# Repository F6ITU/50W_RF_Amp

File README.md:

# 50W_RF_Amp, Codename Diomedes

Diomedes is a 47 dBm (50W) HF amplifier designed by Manfred XQ6FOD, and intended to be used with any baseband SDR delivering no more than 5 to 10 dBm of  output power between 1 and 54 MHz. 

The original schematic of this project 

https://ludens.cl/Electron/50Wamp/RP50Wampwm.png

as well as the assembly instructions are available at the following URL

https://ludens.cl/Electron/50Wamp/50Wamp.html

This github repository only serves to simplify the work of people who want to build this amplifier. It offers  them the Gerber files and the KiCad implementation of this project.

Thank you, Manfred, for the many developments you’ve done around the Red Pitaya board, and especially for your work on the EER support. It’s a « must read »… at least.

This amplifier is designed to follow a 14 or 16 bit Red Pitaya board or any barefoot DDC/DUC SDR board. It completes the series of devices constituting the Alexiares frontend developed by the OpenHPSDR group

https://wiki.electrolab.fr/Projets:Lab:2017:Peripheriques_Angelia

and replaces advantageously the old and outdated  Pennywhistle linear amplifier 

https://openhpsdr.org/pennywhistle.php

It should be noted that board's dimensions and mounting holes are completely compatible with Pennywhistle physical and mechanical design. In fact, Diomedes has been designed as a substitute amplifier. 
The only major difference is the input allowed power (9 dBm for Diomedes, 27 dBm max for Pennywhistle).

More powerful, more sensitive, less expensive, modern, this final stage uses a tandem of LDMOS transistors. It is perfectly matched with the Alex low pass filter 

https://wiki.electrolab.fr/Projets:Lab:2017:Peripheriques_Angelia#Alexiares_lpf

The code name Diomede was given to this amplifier to match the OpenHPSDR naming scheme. 
Diomedes, hero of the Illiad, was one of the most powerful warrior of the Argian clan, opponent of Apollo the defender of Troy. Apollo is the code name of the very first amplifier and low-pass filter tanddem proposed by the OpenHPSDR 

https://openhpsdr.org/apollo.php

So far, this github project is still under development, as long as the first Diomedes PCB  hasn’t been assembled and tested. Do NOT use these Gerber files for the moment.

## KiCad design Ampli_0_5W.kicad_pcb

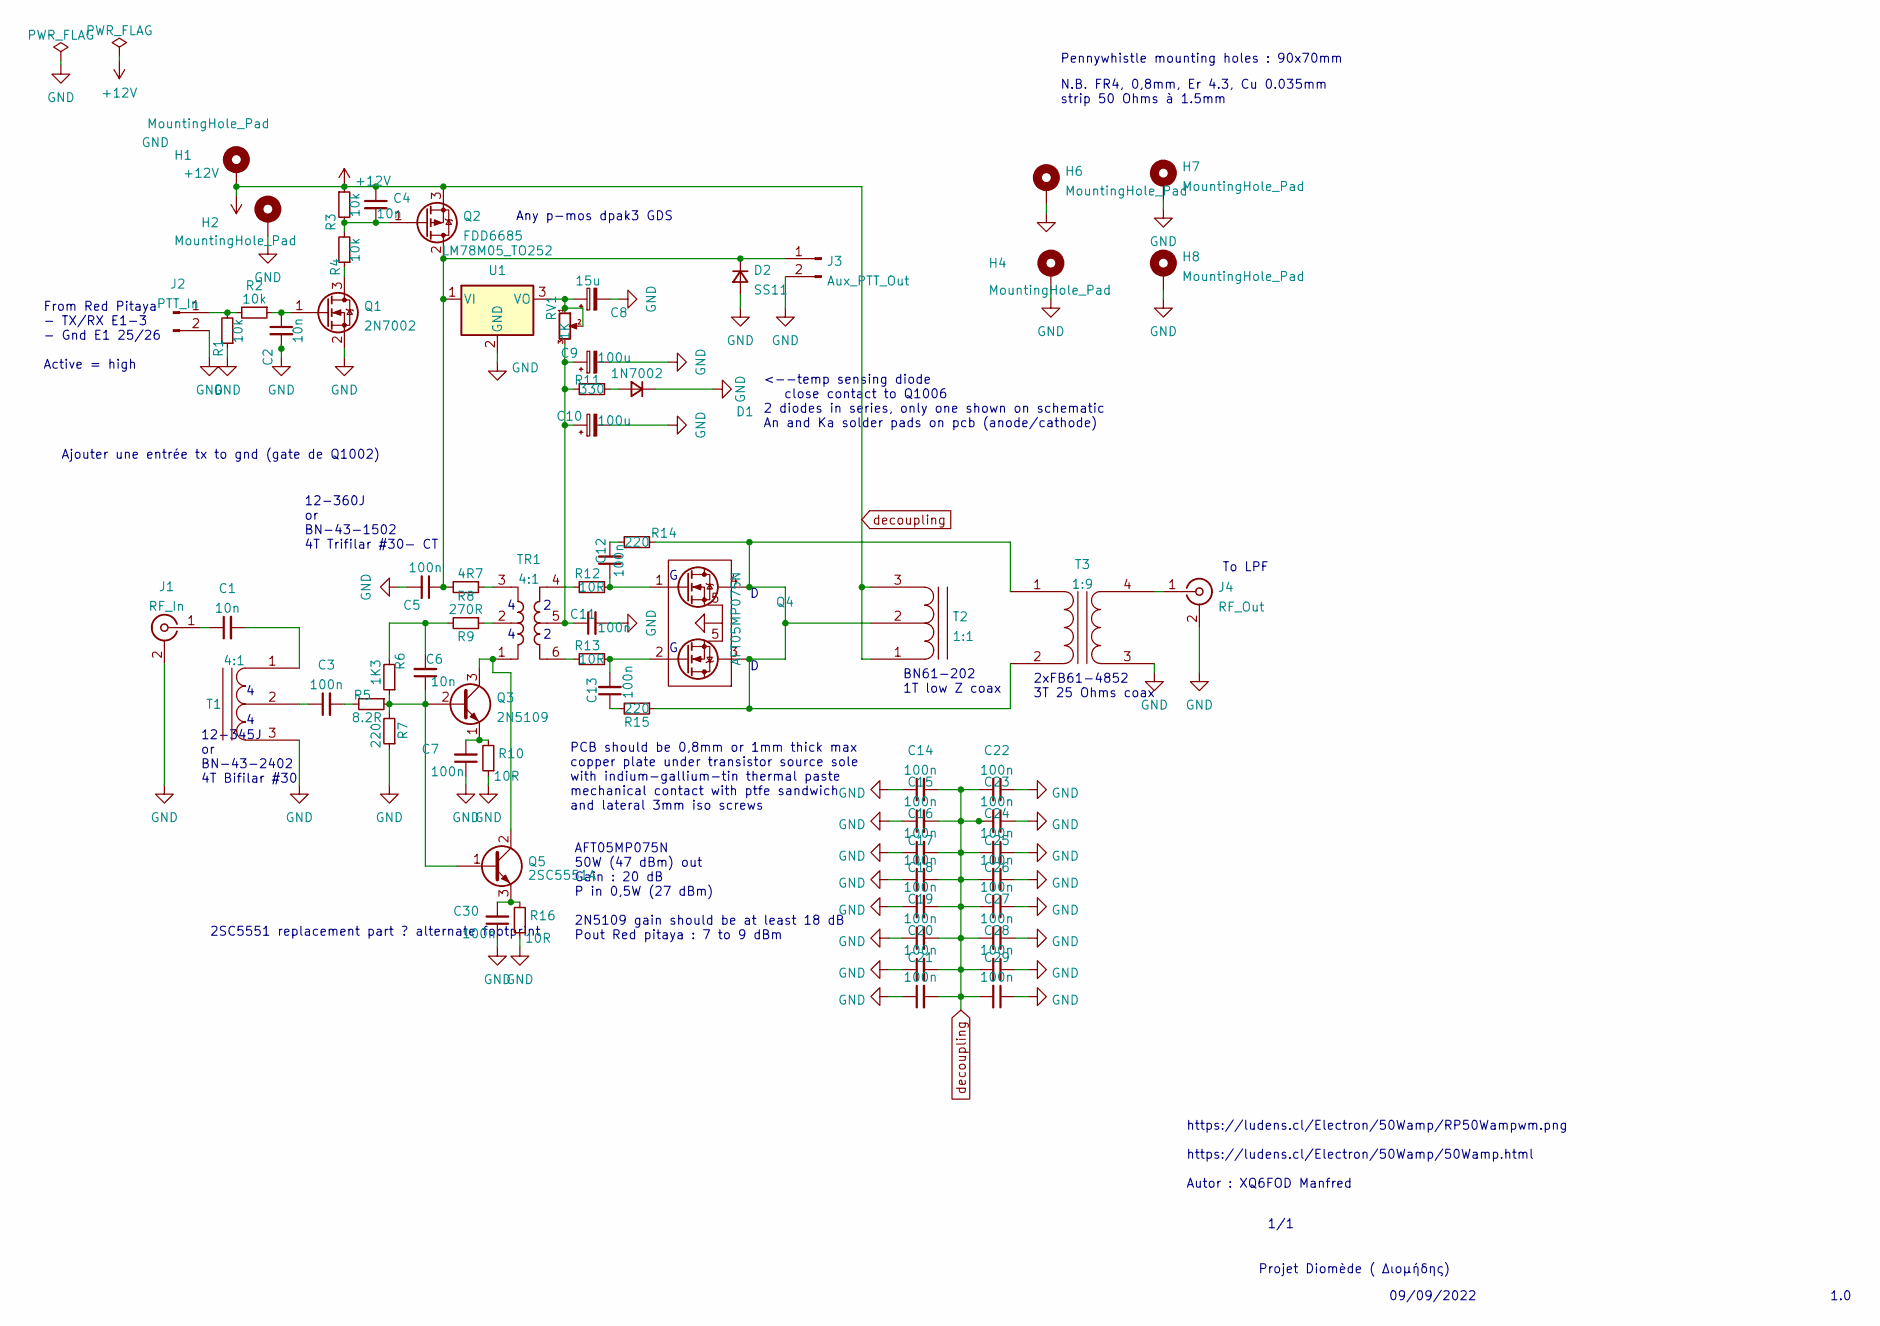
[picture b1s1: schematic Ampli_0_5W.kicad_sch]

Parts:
C1, C2, C4, C6: 10n; C_0805_2012Metric_Pad1.18x1.45mm_HandSolder
C3, C5, C7, C11: 100n; C_0805_2012Metric_Pad1.18x1.45mm_HandSolder
C8: 15u; CP_EIA-6032-28_Kemet-C_Pad2.25x2.35mm_HandSolder
C9, C10: 100u; CP_EIA-7343-31_Kemet-D_Pad2.25x2.55mm_HandSolder
C12, C13: 100n; C_1206_3216Metric_Pad1.33x1.80mm_HandSolder
C14, C15, C16, C17, C18, C19, C20, C21, C22, C23, C24, C25, C26, C27, C28, C29: 100n; C_1210_3225Metric_Pad1.33x2.70mm_HandSolder
C30: 100n; C_0603_1608Metric_Pad1.08x0.95mm_HandSolder
D1: 1N7002; D_2114_3652Metric_Pad1.85x3.75mm_HandSolder
D2: SS11; D_1812_4532Metric_Pad1.30x3.40mm_HandSolder
H1, H2, H4, H6, H7, H8: MountingHole_Pad; MountingHole_3.2mm_M3_DIN965_Pad
J1: RF_In; SMA_PINS
J2: PTT_In; Molex_KK-254_AE-6410-02A_1x02_P2.54mm_Vertical
J3: Aux_PTT_Out; Molex_KK-254_AE-6410-02A_1x02_P2.54mm_Vertical
J4: RF_Out; SMA_PINS
Q1: 2N7002; SOT-23_Handsoldering
Q2: FDD6685; TO-252-2
Q3: 2N5109; TO-39-3
Q4: AFT05MP075N
Q5: 2SC5551A; SOT-89-3
R1, R2, R3, R4: 10k; R_0805_2012Metric_Pad1.20x1.40mm_HandSolder
R5: 8.2R; R_0805_2012Metric_Pad1.20x1.40mm_HandSolder
R6: 1K3; R_0805_2012Metric_Pad1.20x1.40mm_HandSolder
R7: 220; R_0805_2012Metric_Pad1.20x1.40mm_HandSolder
R8: 4R7; R_0805_2012Metric_Pad1.20x1.40mm_HandSolder
R9: 270R; R_0805_2012Metric_Pad1.20x1.40mm_HandSolder
R10, R12, R13: 10R; R_0805_2012Metric_Pad1.20x1.40mm_HandSolder
R11: 330; R_0805_2012Metric_Pad1.20x1.40mm_HandSolder
R14, R15: 220; R_2816_7142Metric_Pad3.20x4.45mm_HandSolder
R16: 10R; R_0603_1608Metric_Pad0.98x0.95mm_HandSolder
RV1: 1K; Potentiometer_Bourns_TC33X_Vertical
T1: 4:1; BN-43-2402
T2: 1:1; BN-61-202
T3: 1:9; Dual_FB-61-4852
TR1: 4:1; BN-43-1502
U1: LM78M05_TO252; TO-252-2

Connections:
GND: C2.2, C5.2, C7.1, C8.2, C9.2, C10.2, C11.2, C14.1, C15.1, C16.1, C17.1, C18.1, C19.1, C20.1, C21.1, C22.1, C23.1, C24.1, C25.1, C26.1, C27.1, C28.1, C29.1, C30.1, D1.1 (K), D2.2 (A), H2.1, H4.1, H6.1, H7.1, H8.1, J1.2 (Ext), J2.2, J3.2, J4.2 (Ext), Q1.2 (S), R1.1, R7.1, R10.1, R16.1, T1.3 (SC), T3.3 (SA), U1.2 (GND)
unnamed: C3.2, R5.2
unnamed: C6.2, R6.2, R9.2
unnamed: C9.1, C10.1, C11.1, R11.2, RV1.3, TR1.5
unnamed: C12.1, Q4.1 (G), R12.1
unnamed: C12.2, R14.2
unnamed: C13.1, R15.2
unnamed: C13.2, Q4.2 (G), R13.1
unnamed: D1.2 (A), R11.1
unnamed: C5.1, D2.1 (K), J3.1, Q2.2 (D), R8.2, U1.1 (VI)
unnamed: C1.1, J1.1 (In)
unnamed: J2.1, R1.2, R2.2
unnamed: J4.1 (In), T3.4 (SB)
unnamed: Q1.3 (D), R4.1
unnamed: C2.1, Q1.1 (G), R2.1
unnamed: C4.2, Q2.1 (G), R3.2, R4.2
unnamed: C6.1, Q3.2 (B), Q5.1 (B), R5.1, R6.1, R7.2
unnamed: Q3.3 (C), Q5.2 (C), TR1.1
unnamed: C7.2, Q3.1 (E), R10.2
unnamed: C30.2, Q5.3 (E), R16.2
unnamed: R8.1, TR1.3
unnamed: R9.1, TR1.2
unnamed: R12.2, TR1.4
unnamed: R13.2, TR1.6
unnamed: C1.2, T1.1 (SA)
unnamed: C3.1, T1.2 (SB)
unnamed: Q4.3 (D), Q4.4 (D), R14.1, R15.1, T2.2 (SB), T3.1 (AA), T3.2 (AB)
unnamed: C8.1, RV1.1, RV1.2, U1.3 (VO)
decoupling: C4.1, C14.2, C15.2, C16.2, C17.2, C18.2, C19.2, C20.2, C21.2, C22.2, C23.2, C24.2, C25.2, C26.2, C27.2, C28.2, C29.2, H1.1, Q2.3 (S), R3.1, T2.1 (SA), T2.3 (SC)

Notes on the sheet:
To LPF
4 4
12-360J or BN-43-1502 4T Trifilar #30- CT
09/09/2022
Projet Diomède ( Διομήδης)
BN61-202 1T low Z coax
AFT05MP075N 50W (47 dBm) out Gain : 20 dB P in 0,5W (27 dBm) 2N5109 gain should be at least 18 dB Pout Red pitaya : 7 to 9 dBm
Pennywhistle mounting holes : 90x70mm
2xFB61-4852 3T 25 Ohms coax
2SC5551 replacement part ? alternate footprint
N.B. FR4, 0,8mm, Er 4.3, Cu 0.035mm strip 50 Ohms à 1.5mm
12-345J or BN-43-2402 4T Bifilar #30
PCB should be 0,8mm or 1mm thick max copper plate under transistor source sole with indium-gallium-tin thermal paste mechanical contact with ptfe sandwich and lateral 3mm iso screws
Ajouter une entrée tx to gnd (gate de Q1002)
1/1
https://ludens.cl/Electron/50Wamp/RP50Wampwm.png https://ludens.cl/Electron/50Wamp/50Wamp.html Autor : XQ6FOD Manfred
2 2
Any p-mos dpak3 GDS
From Red Pitaya - TX/RX E1-3 - Gnd E1 25/26 Active = high
D D
<--temp sensing diode close contact to Q1006 2 diodes in series, only one shown on schematic An and Ka solder pads on pcb (anode/cathode)
1.0
G G

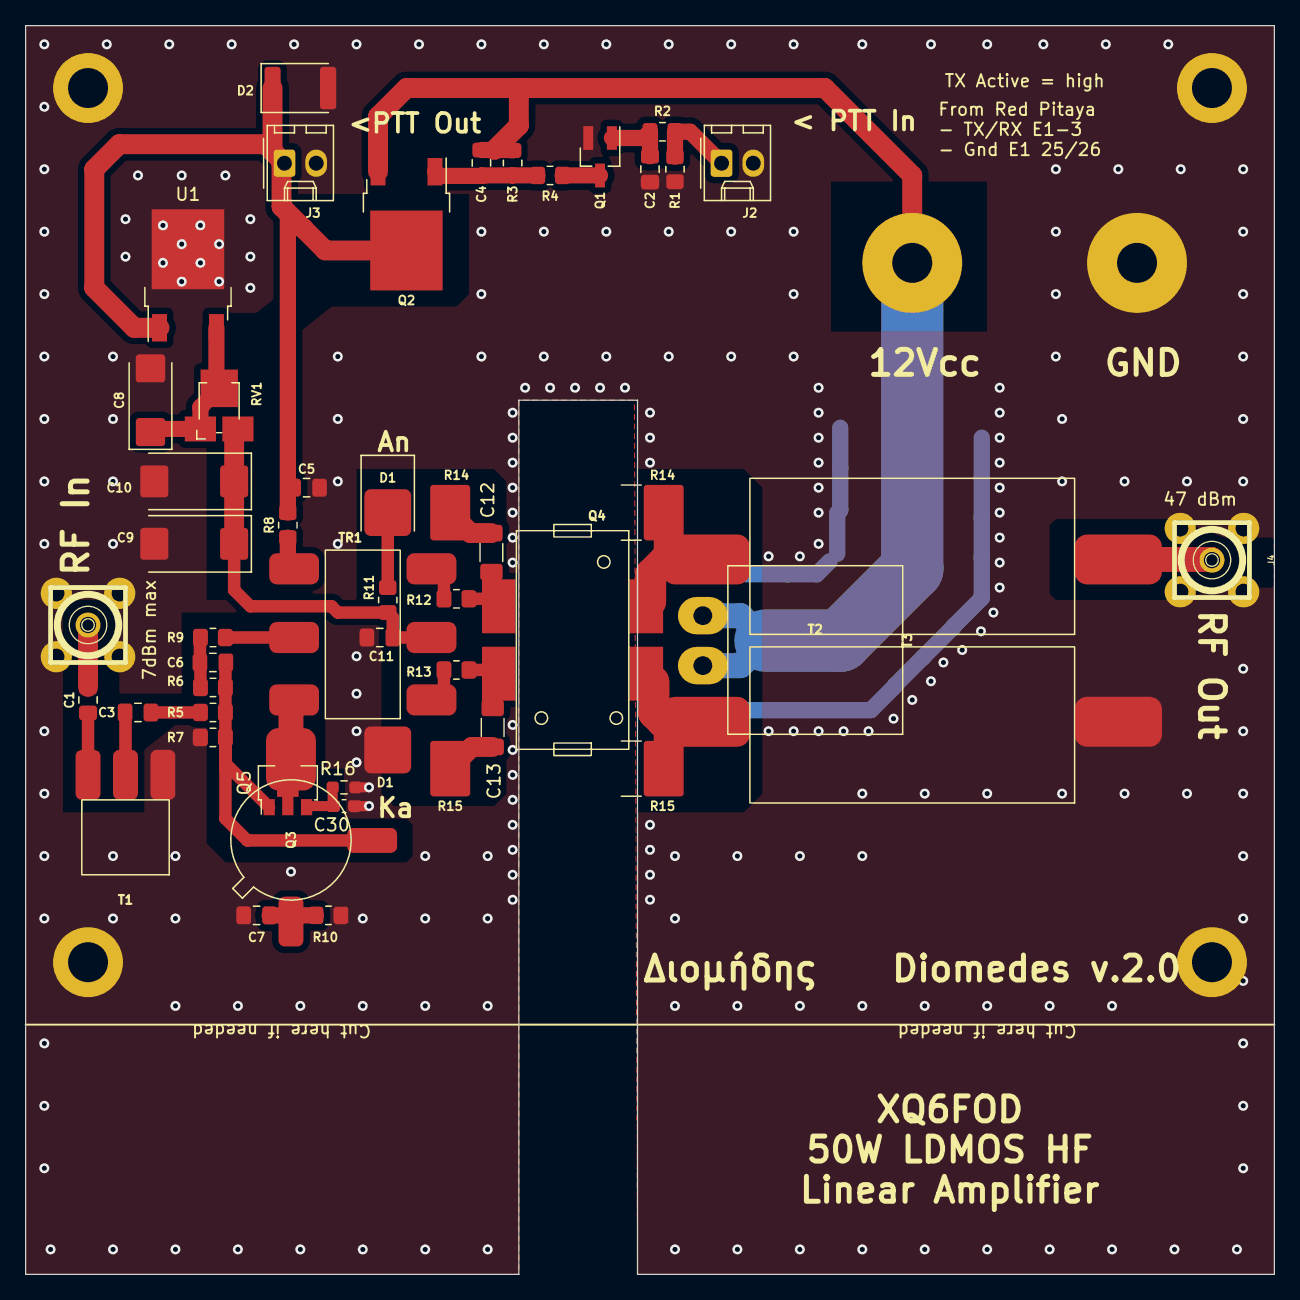
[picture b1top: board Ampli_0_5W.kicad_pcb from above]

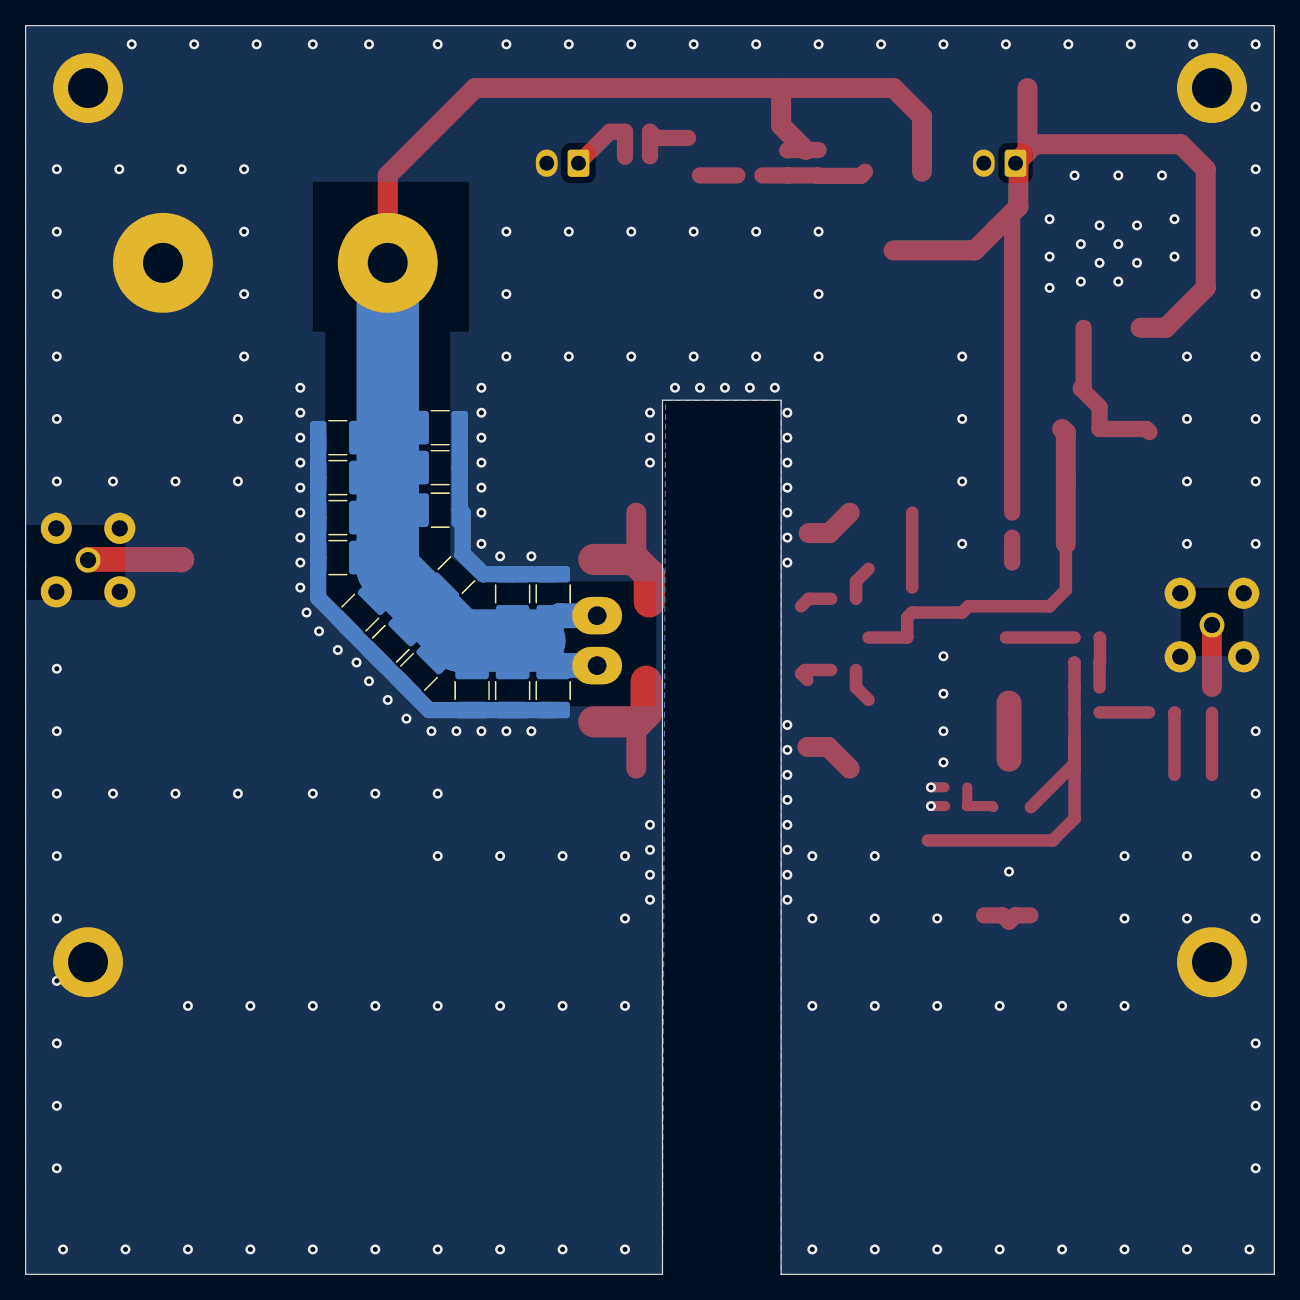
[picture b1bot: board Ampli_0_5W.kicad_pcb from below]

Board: 2 copper layers, 100.0 x 100.0 mm, 69 parts (16 on the bottom side), 29 nets.

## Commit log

2022-09-09 first commit before proto
2022-09-09 picture and pdf schematic added
2022-09-09 minor corrections
2022-09-18 release 2.0, shorter drain path
2022-09-27 shorten drain circuit, new gerber, new ibom
2022-10-12 PCB V2 final
2023-02-12 Diomedes V1.0 final with correct psu, bias & drain trace
2023-02-12 new 3D rendering
2023-02-12 new V1.0 Gerber, new ReadMe
2023-02-12 Diomedes V2.0 final, bias OK
2023-02-14 new ibom, BEWARE, KICAD 7.0 FILE FORMAT
2023-02-14 Kicad 7, new iBom, new temp diode cabling
2023-02-14 temp diode 3D model modified, new ibom new gerber
2023-02-14 new png, new iBom
2023-02-17 pennywhistle compatible mounting holes
2023-02-17 new 3D image, minor changes
2023-02-17 new pdf schematic with dual BJT transistor
2023-03-31 new slotted pcb, new transistor added
